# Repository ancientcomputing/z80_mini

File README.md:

Monitor/Debugger and BASIC for Bernd Ulmann's z80_mini (http://www.vaxman.de/projects/Z80_mini/index.html)
<p>
Binary files are minimon.rom (Monitor/Debugger) and minimonbas.rom (Monitor/Debugger and BASIC).
<p>
This version of software has been built for the Z80_mini Rev B board. It uses interrupts to signal when incoming characters are available. Interrupts may not work with the original Z80_mini board.
<p>
The software also changes the baud rate generator to assume a 7.3728MHz UART crystal and to achieve 115200 baudrate.
<p>
The User Guide is at https://github.com/ancientcomputing/rc2014/tree/master/docs<p>
Everything here is built on the contributions of many people. Acknowledgements are in the source code.
<p>
<hr>
<p>
Blog: http://ancientcomputing.blogspot.com/

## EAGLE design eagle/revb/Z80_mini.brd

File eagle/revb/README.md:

Z80_mini Rev B Board
<p>
This is Rev B of Bernd Ulmann's z80_mini board design.
<p>
Key changes include:<br>
- Elimination of power connector<br>
- Elimination of traditional RS232 connection<br>
- Use of FTDI connector for serial and power<br>
- Addition of jumpers to allow use of 28C256 EEPROM<br>
- Proper CTS/RTS wiring<br>
- Proper UART chipselect with M1 signal<br>
- Bring out the spare UART OUT1 and OUT2 signals to a header for other uses e.g. audio out etc.<br>
<p>All rights of the original work is acknowledged. Changes/mods are copyright Ben Chong and licensed freely to the community.
<p>
The board is available at OSH Park. Note that I don't have any relationship with OSH Park except that of a customer.
<p>
<a href="https://www.oshpark.com/shared_projects/yrpH1AFt"></img></a>
<p>

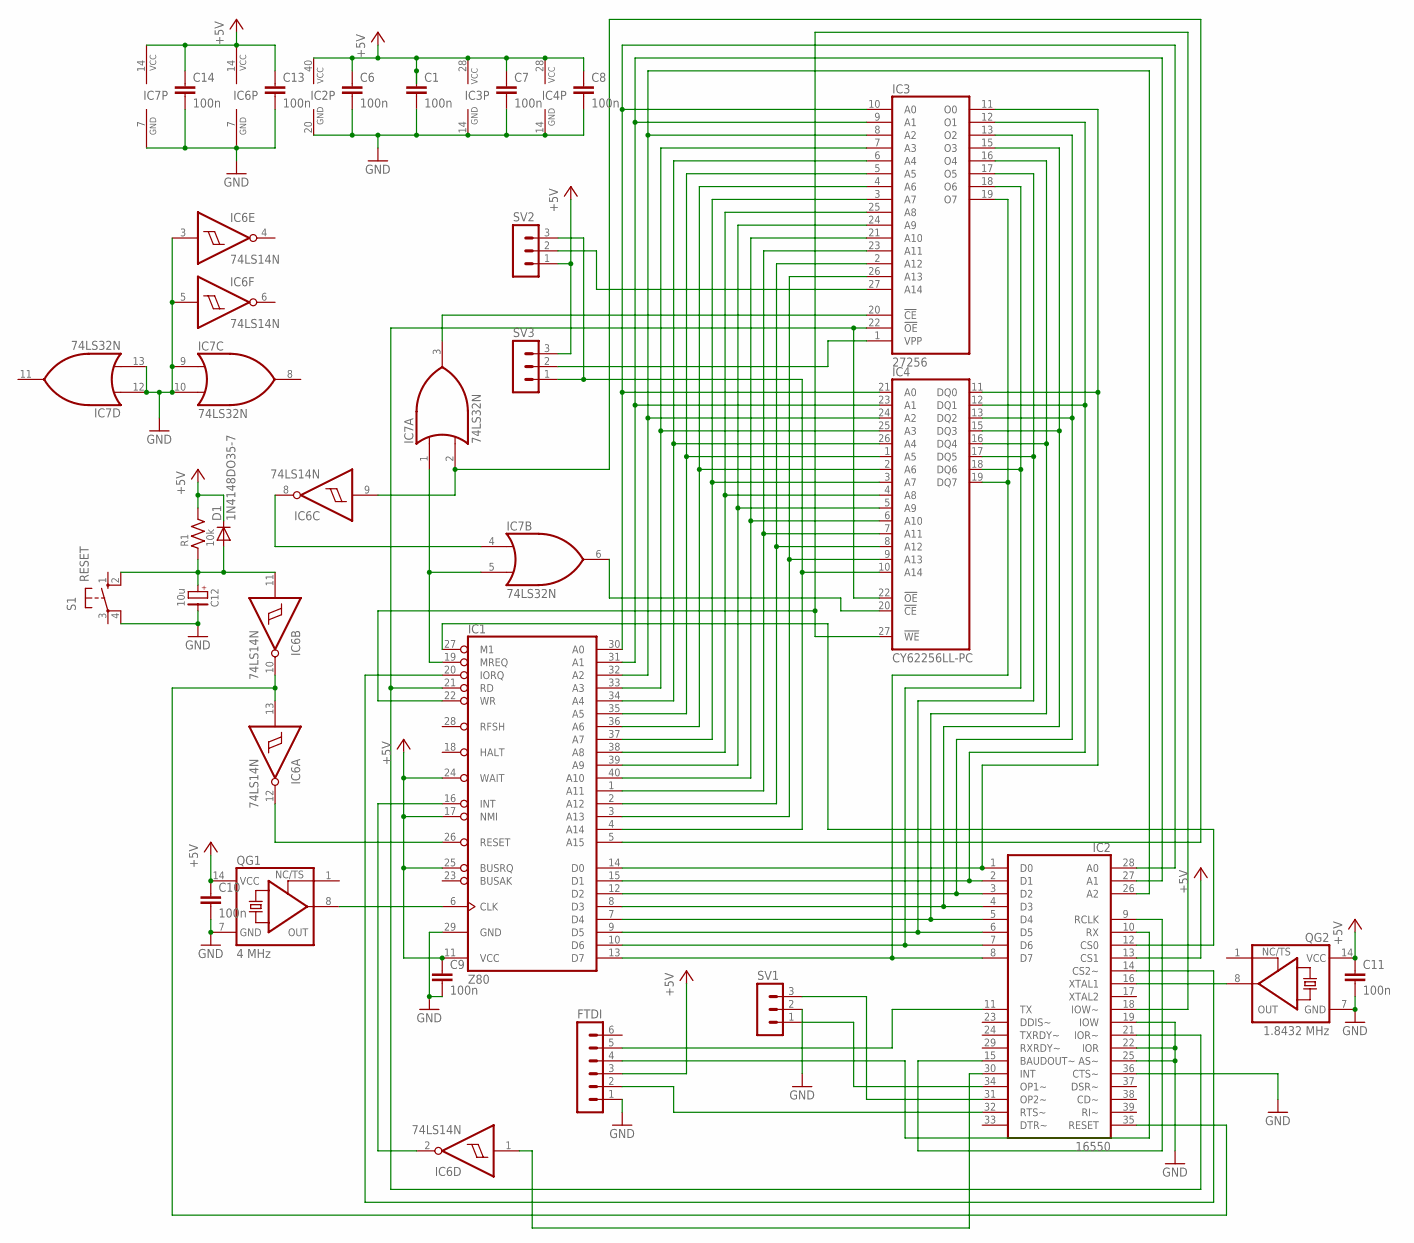
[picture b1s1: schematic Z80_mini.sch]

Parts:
C1, C6, C7, C8, C9, C10, C11, C13, C14: 100n; C5B2.5
C12: 10u; CE01A
D1: 1N4148DO35-7; DO35-7
FTDI: MA06-1
IC1: Z80; DIL40
IC2: 16550; DIL40
IC3: 27256; DIL28
IC4: CY62256LL-PC; DIL28-6
IC6: 74LS14N; DIL14
IC7: 74LS32N; DIL14
QG1: 4 MHz; DIL14S
QG2: 1.8432 MHz; DIL14S
R1: 10k; R04N
S1: RESET; B3F-10XX
SV1, SV2, SV3: MA03-1

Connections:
+5V: C1.1, C6.1, C7.1, C8.1, C9.1, C10.1, C11.1, C13.1, C14.1, D1.C, FTDI.3, IC1.11 (VCC), IC1.17 (NMI), IC1.24 (WAIT), IC1.25 (BUSRQ), IC2.13 (CS1), IC2.40 (VCC), IC3.28 (VCC), IC4.28 (VCC), IC6.14 (VCC), IC7.14 (VCC), QG1.14 (VCC), QG2.14 (VCC), R1.2, SV2.1, SV3.3
GND: C1.2, C6.2, C7.2, C8.2, C9.2, C10.2, C11.2, C12.-, C13.2, C14.2, FTDI.1, IC1.29 (GND), IC2.19 (IOW), IC2.20 (GND), IC2.22 (IOR), IC2.25 (AS~), IC2.36 (CTS~), IC3.14 (GND), IC4.14 (GND), IC6.3 (I), IC6.5 (I), IC6.7 (GND), IC7.7 (GND), IC7.9 (I0), IC7.10 (I1), IC7.12 (I0), IC7.13 (I1), QG1.7 (GND), QG2.7 (GND), S1.4 (P1), SV1.2
unnamed: IC1.14 (D0), IC2.1 (D0), IC3.11 (O0), IC4.11 (DQ0)
unnamed: IC1.15 (D1), IC2.2 (D1), IC3.12 (O1), IC4.12 (DQ1)
unnamed: IC1.12 (D2), IC2.3 (D2), IC3.13 (O2), IC4.13 (DQ2)
unnamed: IC1.8 (D3), IC2.4 (D3), IC3.15 (O3), IC4.15 (DQ3)
unnamed: IC1.7 (D4), IC2.5 (D4), IC3.16 (O4), IC4.16 (DQ4)
unnamed: IC1.9 (D5), IC2.6 (D5), IC3.17 (O5), IC4.17 (DQ5)
unnamed: IC1.10 (D6), IC2.7 (D6), IC3.18 (O6), IC4.18 (DQ6)
unnamed: IC1.13 (D7), IC2.8 (D7), IC3.19 (O7), IC4.19 (DQ7)
unnamed: IC1.30 (A0), IC2.28 (A0), IC3.10 (A0), IC4.21 (A0)
unnamed: IC1.31 (A1), IC2.27 (A1), IC3.9 (A1), IC4.23 (A1)
unnamed: IC1.32 (A2), IC2.26 (A2), IC3.8 (A2), IC4.24 (A2)
unnamed: IC1.33 (A3), IC3.7 (A3), IC4.25 (A3)
unnamed: IC1.34 (A4), IC3.6 (A4), IC4.26 (A4)
unnamed: IC1.35 (A5), IC3.5 (A5), IC4.1 (A5)
unnamed: IC1.36 (A6), IC3.4 (A6), IC4.2 (A6)
unnamed: IC1.37 (A7), IC3.3 (A7), IC4.3 (A7)
unnamed: IC1.38 (A8), IC3.25 (A8), IC4.4 (A8)
unnamed: IC1.39 (A9), IC3.24 (A9), IC4.5 (A9)
unnamed: IC1.40 (A10), IC3.21 (A10), IC4.6 (A10)
unnamed: IC1.1 (A11), IC3.23 (A11), IC4.7 (A11)
unnamed: IC1.2 (A12), IC3.2 (A12), IC4.8 (A12)
unnamed: IC1.3 (A13), IC3.26 (A13), IC4.9 (A13)
unnamed: IC1.4 (A14), IC4.10 (A14), SV2.3, SV3.1
unnamed: FTDI.4, IC2.10 (RX)
unnamed: IC1.21 (RD), IC2.21 (IOR~), IC3.22 (!OE), IC4.22 (!OE)
unnamed: IC1.22 (WR), IC2.18 (IOW~), IC4.27 (!WE)
unnamed: IC1.27 (M1), IC2.12 (CS0)
unnamed: FTDI.2, IC2.32 (RTS~)
unnamed: IC3.1 (VPP), SV3.2
unnamed: FTDI.5, IC2.11 (TX)
unnamed: IC3.27 (A14), SV2.2
unnamed: IC2.31 (OP2~), SV1.3
unnamed: IC2.34 (OP1~), SV1.1
unnamed: IC1.6 (CLK), QG1.8 (OUT)
unnamed: IC1.26 (RESET), IC6.12 (O)
unnamed: IC2.16 (XTAL1), QG2.8 (OUT)
unnamed: IC2.9 (RCLK), IC2.15 (BAUDOUT~)
unnamed: IC1.20 (IORQ), IC2.14 (CS2~)
unnamed: IC2.35 (RESET), IC6.10 (O), IC6.13 (I)
unnamed: C12.+, D1.A, IC6.11 (I), R1.1, S1.2 (S1)
unnamed: IC1.19 (MREQ), IC7.1 (I0), IC7.5 (I1)
unnamed: IC3.20 (!CE), IC7.3 (O)
unnamed: IC6.8 (O), IC7.4 (I0)
unnamed: IC4.20 (!CE), IC7.6 (O)
unnamed: IC2.30 (INT), IC6.1 (I)
unnamed: IC1.16 (INT), IC6.2 (O)
unnamed: IC1.5 (A15), IC6.9 (I), IC7.2 (I1)

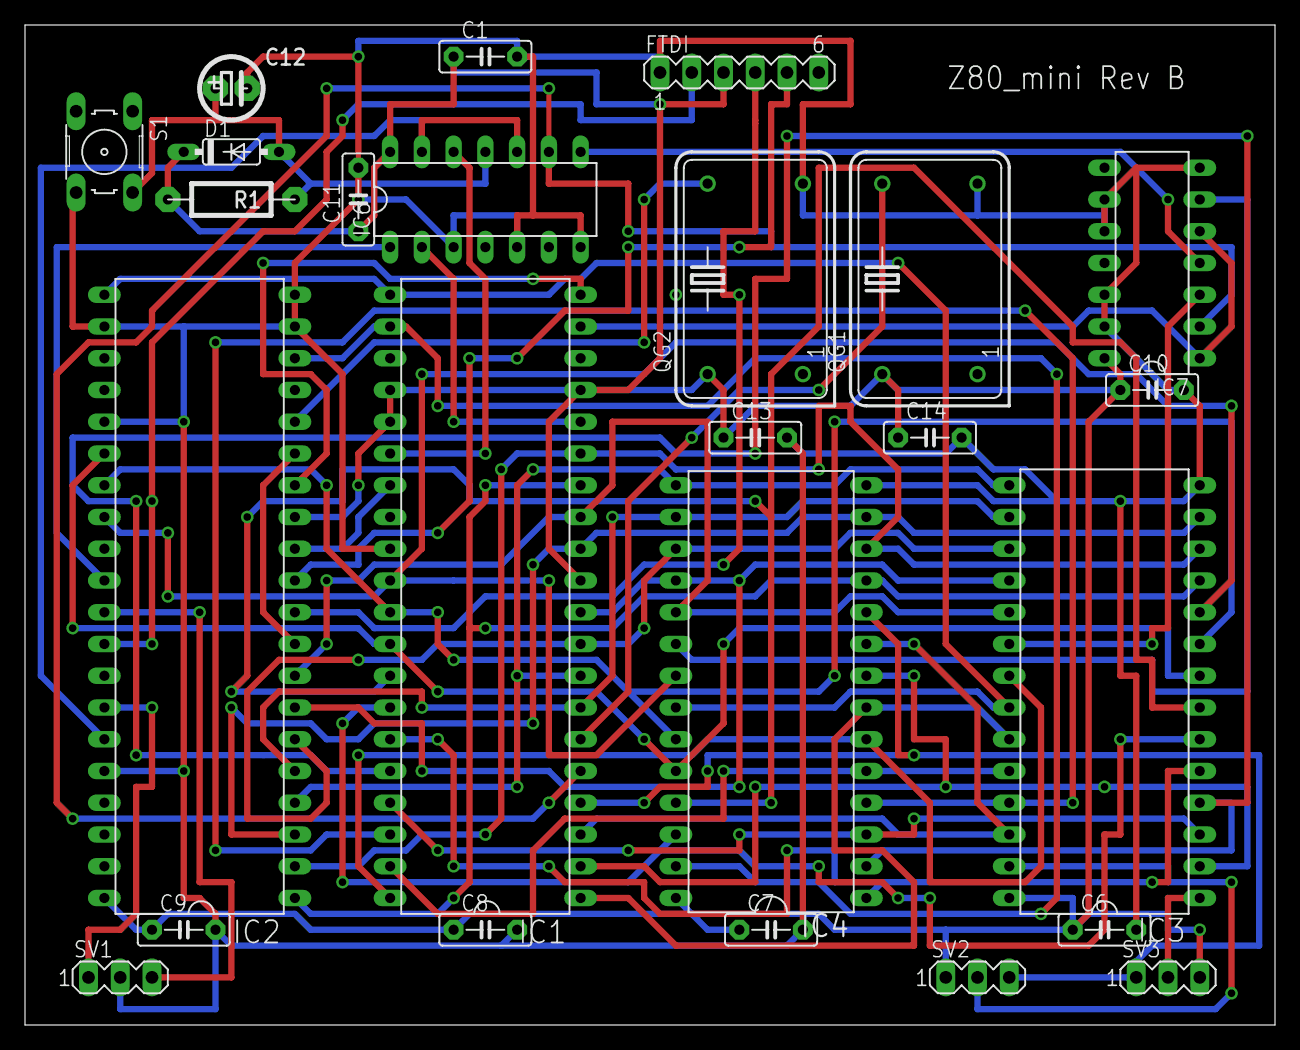
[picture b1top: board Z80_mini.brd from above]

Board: 2 copper layers, 100.0 x 80.0 mm, 25 parts (0 on the bottom side), 49 nets.

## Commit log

2017-04-02 Add interrupt handler code
2017-04-02 Add tools to set baudrate, enable autoflow control
2017-04-02 Add routines to enable AFE and set baudrate
2017-04-02 Remove serial interrupt handler, fix entry points for setbaud and setafe
2017-04-02 Added notes for stuff in /tools
2017-04-07 Enable RTS line during init
2017-04-08 Stuff return address on stack when using G command so that you can RET back to the Monitor
2017-04-17 Consolidate with RC2014 monitor
2017-04-21 Z80_mini Rev B board
2017-04-21 Update README with link to OSH Park
2017-04-22 Use UART interrupts and 255-byte receive buffer
